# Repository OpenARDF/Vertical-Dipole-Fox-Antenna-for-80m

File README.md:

# Vertical Dipole Fox Antenna for 80m
 A short vertical antenna designed for ARDF.

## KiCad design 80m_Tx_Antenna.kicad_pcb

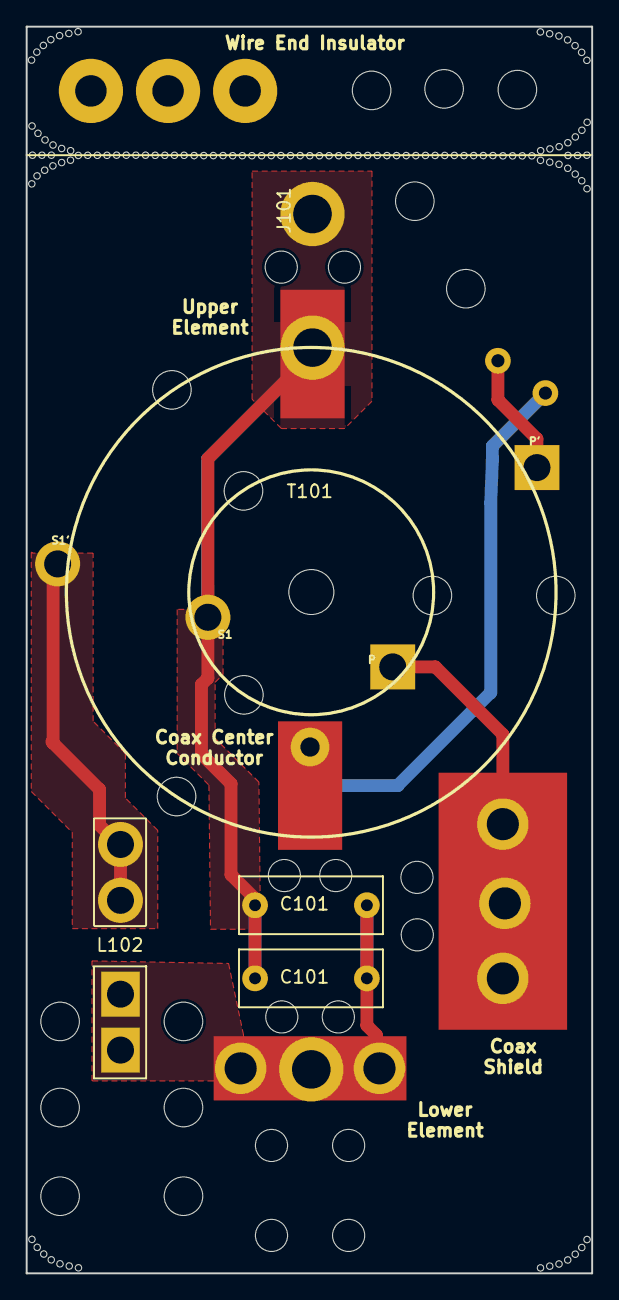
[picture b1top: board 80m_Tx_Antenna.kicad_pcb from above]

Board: 2 copper layers, 44.0 x 97.0 mm, 7 parts (1 on the bottom side), 6 nets.

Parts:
C101, C101#2: 470pF; C_Disc_D7.5_P5
J101: Thru Holes; Wire_Strain_Relief_and_Attach
J103: CONN_01X03; RG-174_Attachment
L101: 3.2uH; Toroid_T-60_2TH
L102: 0.4-1.0uH; Manually_Wound_Coil
T101: TRANSFO; Core_150A_2_windings_Horiz_TH

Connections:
unnamed: C101.1, C101#2.1, J101.1, T101.4
unnamed: C101.2, C101#2.2, J103.3, L102.1
unnamed: J103.1, L101.2
unnamed: J103.2, T101.2
unnamed: L101.1, T101.1
unnamed: L102.2, T101.3

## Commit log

2024-02-12 16 July 2021
    Initial commit
2024-02-13 Reorganization
    Put files into folder
2024-02-13 Reorganization
    Moved README
2024-02-13 Moved License
